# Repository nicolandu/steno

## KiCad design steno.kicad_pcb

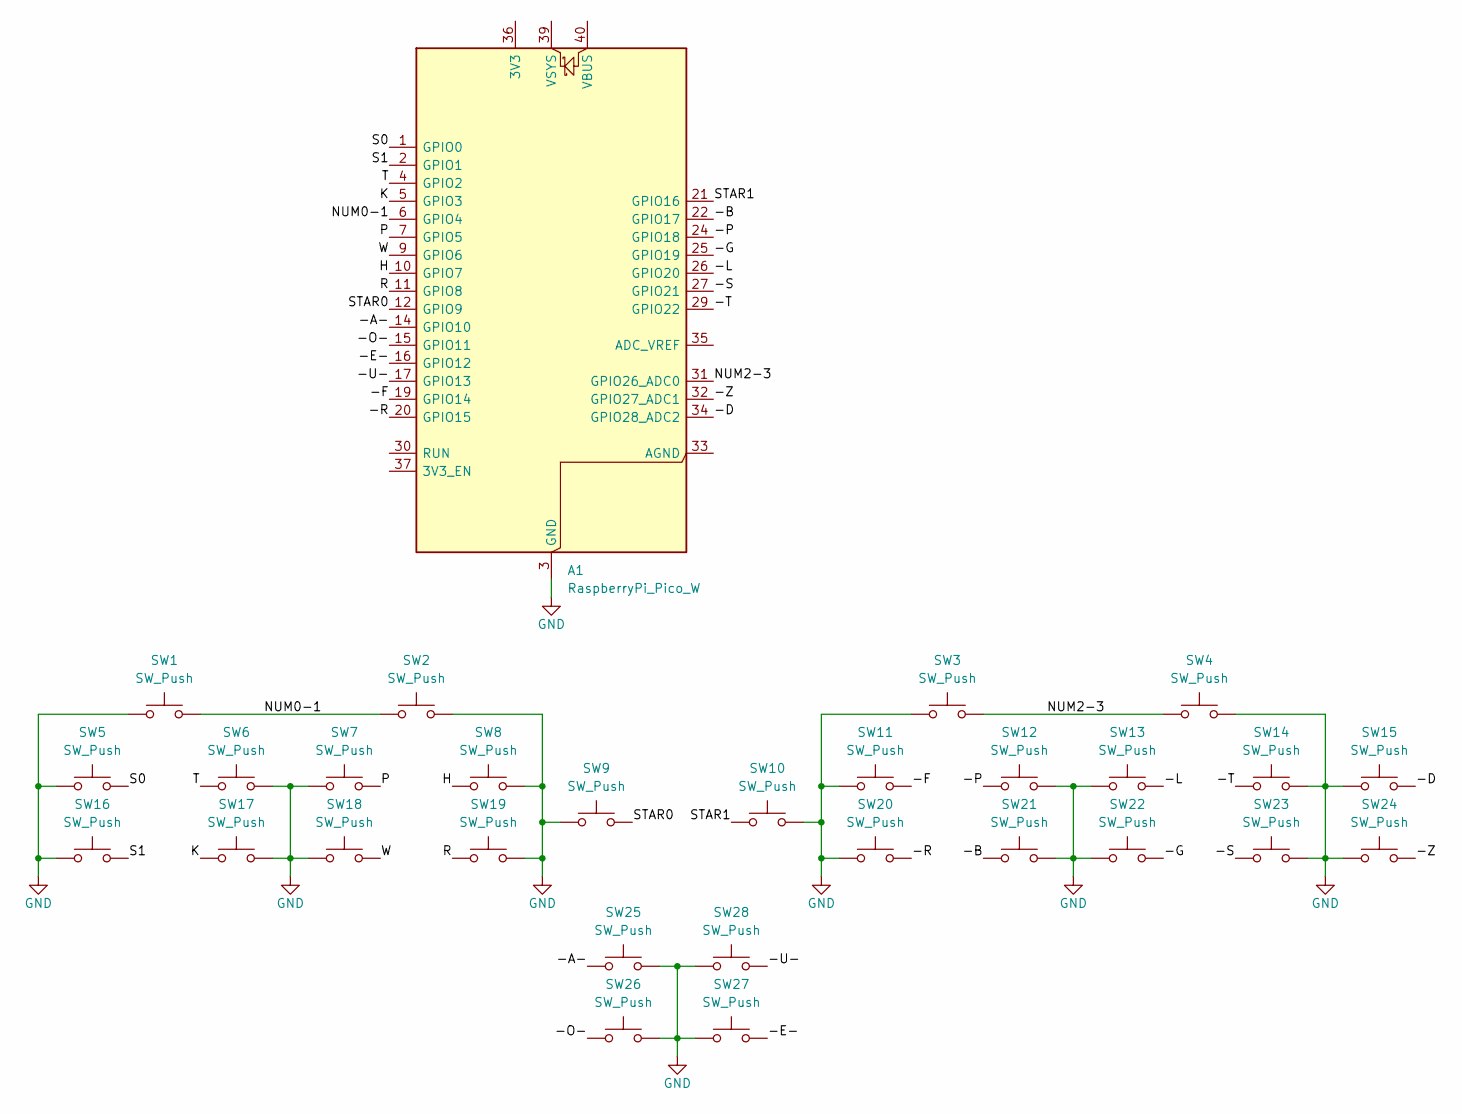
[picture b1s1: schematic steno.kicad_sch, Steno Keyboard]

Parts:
A1: RaspberryPi_Pico_W; RaspberryPi_Pico_Common
SW1, SW2, SW3, SW4, SW9, SW10: SW_Push; SW_Cherry_MX_2.00u_PCB
SW5, SW6, SW7, SW8, SW11, SW12, SW13, SW14, SW15, SW16, SW17, SW18, SW19, SW20, SW21, SW22, SW23, SW24, SW25, SW26, SW27, SW28: SW_Push; SW_Cherry_MX_1.00u_PCB

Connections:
/-A-: A1.14 (GPIO10), SW25.2
/-B: A1.22 (GPIO17), SW21.2
/-D: A1.34 (GPIO28_ADC2), SW15.2
/-E-: A1.16 (GPIO12), SW27.2
/-F: A1.19 (GPIO14), SW11.2
/-G: A1.25 (GPIO19), SW22.2
/-L: A1.26 (GPIO20), SW13.2
/-O-: A1.15 (GPIO11), SW26.2
/-P: A1.24 (GPIO18), SW12.2
/-R: A1.20 (GPIO15), SW20.2
/-S: A1.27 (GPIO21), SW23.2
/-T: A1.29 (GPIO22), SW14.2
/-U-: A1.17 (GPIO13), SW28.2
/-Z: A1.32 (GPIO27_ADC1), SW24.2
/H: A1.10 (GPIO7), SW8.2
/K: A1.5 (GPIO3), SW17.2
/NUM0-1: A1.6 (GPIO4), SW1.2, SW2.2
/NUM2-3: A1.31 (GPIO26_ADC0), SW3.2, SW4.2
/P: A1.7 (GPIO5), SW7.2
/R: A1.11 (GPIO8), SW19.2
/S0: A1.1 (GPIO0), SW5.2
/S1: A1.2 (GPIO1), SW16.2
/STAR0: A1.12 (GPIO9), SW9.2
/STAR1: A1.21 (GPIO16), SW10.2
/T: A1.4 (GPIO2), SW6.2
/W: A1.9 (GPIO6), SW18.2
GND: A1.3 (GND), A1.8 (GND), A1.13 (GND), A1.18 (GND), A1.23 (GND), A1.28 (GND), A1.38 (GND), SW1.1, SW2.1, SW3.1, SW4.1, SW5.1, SW6.1, SW7.1, SW8.1, SW9.1, SW10.1, SW11.1, SW12.1, SW13.1, SW14.1, SW15.1, SW16.1, SW17.1, SW18.1, SW19.1, SW20.1, SW21.1, SW22.1, SW23.1, SW24.1, SW25.1, SW26.1, SW27.1, SW28.1

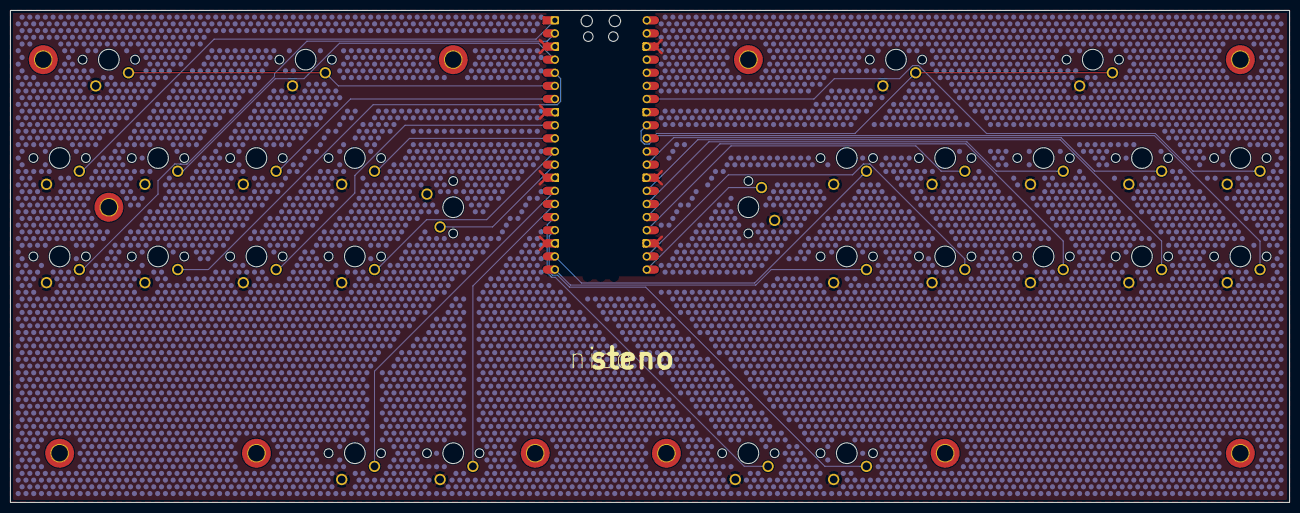
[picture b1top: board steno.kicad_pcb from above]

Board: 2 copper layers, 247.6 x 95.3 mm, 29 parts (0 on the bottom side), 27 nets.

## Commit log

2024-07-30 Continue schematic
2024-07-30 Start routing
2024-07-30 Finish routing
2024-07-30 Change outline shape
2024-08-03 Finalized routing, added mounting holes
2024-08-05 Finalised design
2025-03-01 Final version
